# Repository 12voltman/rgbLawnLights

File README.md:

# rgbLawnLights
Circuit boards for a distributed network of individually adressable RGB led bulbs.

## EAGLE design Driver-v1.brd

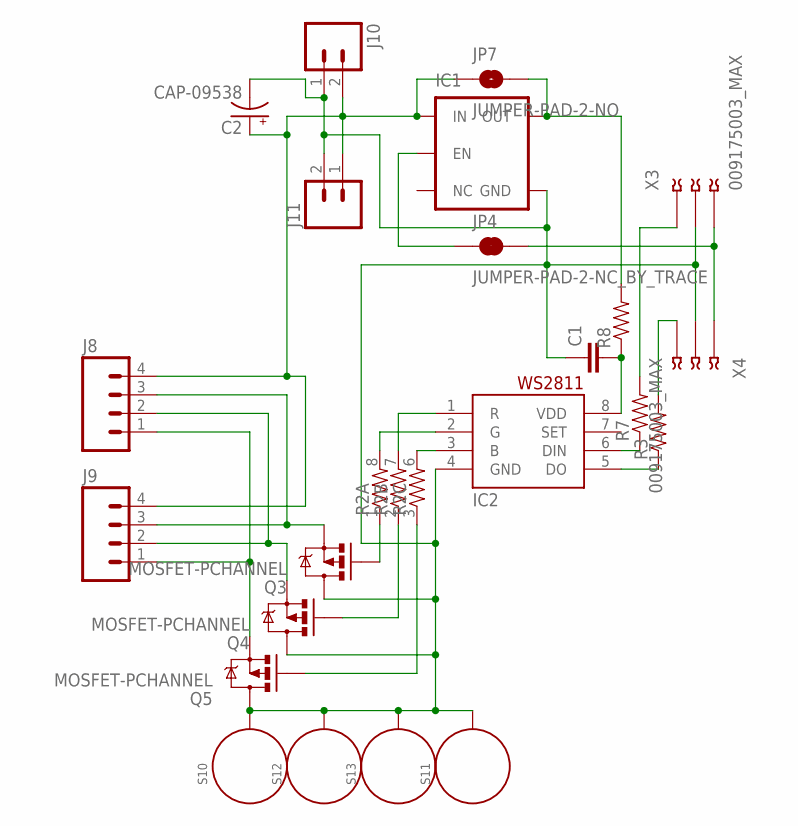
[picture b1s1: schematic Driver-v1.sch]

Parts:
C1: CAP1206; 1206
C2: CAP-09538; CPOL-RADIAL-1000UF-25V
IC1: V_REG_TPS76433SOT23-5; SOT23-5
IC2: WS2811-SOP8; SO08-SKINNYPADS
J8, J9: M04LONGPADS; 1X04_LONGPADS
J10, J11: M025MM; SCREWTERMINAL-5MM-2
JP4: JUMPER-PAD-2-NC_BY_TRACE; PAD-JUMPER-2-NC_BY_TRACE_YES_SILK
JP7: JUMPER-PAD-2-NO; PAD-JUMPER-2-NO_NO_SILK
Q3, Q4, Q5: MOSFET-PCHANNEL; SOT23-3
R2: RESISTOR-ARRAY0603-ARV; 0603-ARV
R3, R7: RESISTOR0603; 0603-RES
R8: RESISTOR0805-RES; 0805
S10, S11, S12, S13: STANDOFF_ELECTRICAL; STANDOFF-ELECTRICAL
X3, X4: 009175003_MAX

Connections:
GND2: C1.1, C2.-, IC1.2 (GND), IC2.4 (GND), J10.1, J11.2, Q3.3 (D), Q4.3 (D), Q5.3 (D), S10.P1, S11.P1, S12.P1, S13.P1, X3.2, X3.2@1 (2), X4.2, X4.2@1 (2)
unnamed: J8.1, J9.1, Q5.2 (S)
unnamed: J8.2, J9.2, Q4.2 (S)
unnamed: J8.3, J9.3, Q3.2 (S)
unnamed: Q3.1 (G), R2.1
unnamed: Q4.1 (G), R2.2 (1)
unnamed: Q5.1 (G), R2.3 (1)
unnamed: JP4.2, X3.3, X3.3@2 (3), X4.1, X4.1@1 (1)
unnamed: IC1.3 (EN), JP4.1
unnamed: R7.2, X3.1, X3.1@1 (1)
unnamed: IC2.5 (DO), R3.1
unnamed: IC2.3 (B), R2.6 (2)
unnamed: IC2.2 (G), R2.8 (2)
unnamed: IC2.1 (R), R2.7 (2)
unnamed: IC1.5 (OUT), JP7.2, R8.2
unnamed: IC2.6 (DIN), R7.1
unnamed: R3.2, X4.3, X4.3@2 (3)
unnamed: C1.2, IC2.8 (VDD), R8.1
VIN2: C2.+, IC1.1 (IN), J8.4, J9.4, J10.2, J11.1, JP7.1

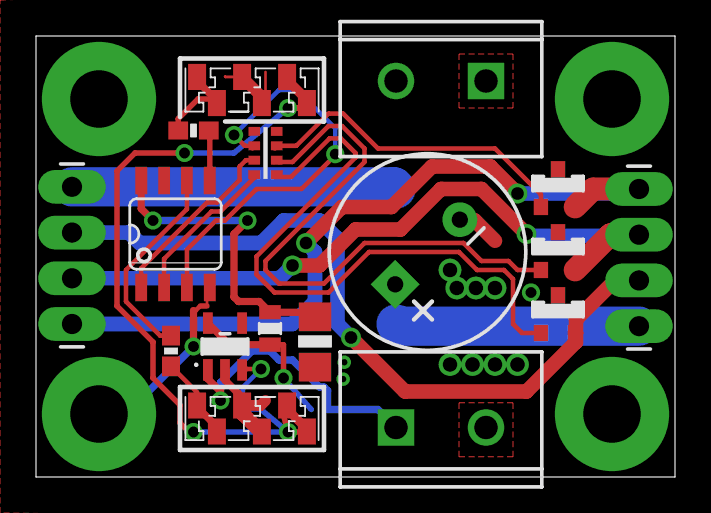
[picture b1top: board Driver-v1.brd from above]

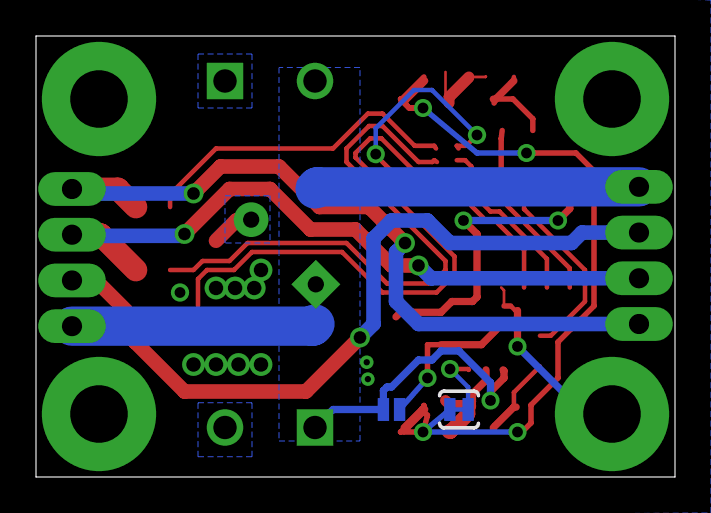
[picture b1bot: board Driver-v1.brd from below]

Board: 2 copper layers, 35.5 x 24.5 mm, 23 parts (2 on the bottom side), 19 nets.

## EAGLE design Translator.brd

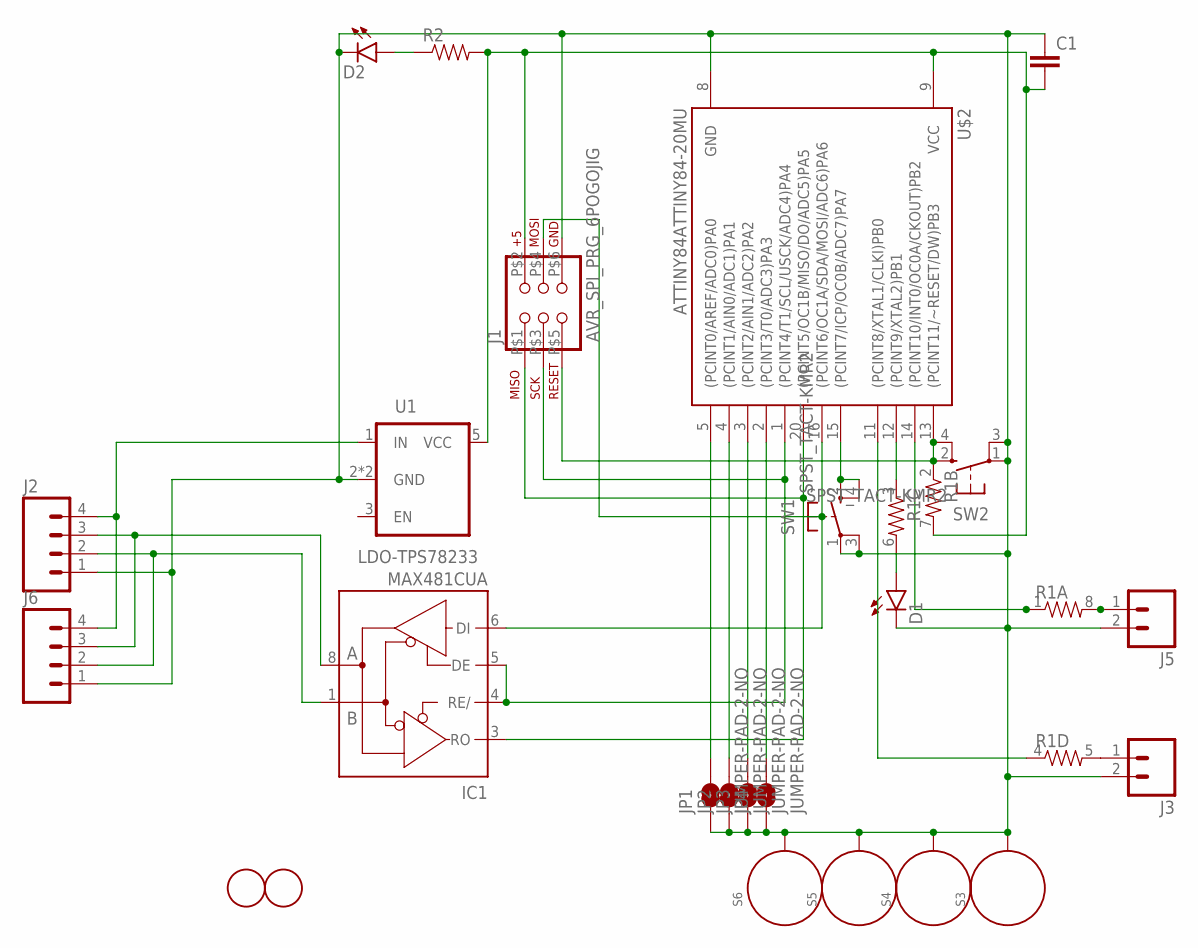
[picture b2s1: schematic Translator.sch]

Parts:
C1: CAP0805; 0805
D1, D2: LED1206; LED-1206
IC1: MAX481CUA; UMAX8
J1: AVR_SPI_PRG_6POGOJIG; 2X3_MAX
J2, J6: M04SCREW; SCREWTERMINAL-3.5MM-4
J3, J5: M025MM; SCREWTERMINAL-5MM-2
JP1, JP2, JP3, JP4: JUMPER-PAD-2-NO; PAD-JUMPER-2-NO_NO_SILK
R1: RESISTOR-ARRAY0603-ARV; 0603-ARV
R2: RESISTOR0805-RES; 0805
S3, S4, S5, S6: STANDOFF_ELECTRICAL; STANDOFF-ELECTRICAL
SW1, SW2: SPST_TACT-KMR2; KMR2
U1: LDO-TPS78233; SOT23-5
U$2: ATTINY84ATTINY84-20MU; QFN20
U$3, U$4: FIDUCIAL; FIDUCIAL_1MM

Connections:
485A: IC1.8 (A), J2.3, J6.3
485B: IC1.1 (B), J2.2, J6.2
FLOW: IC1.4 (RE/), IC1.5 (DE), J1.P$3 (SCK), U$2.1 ((PCINT4/T1/SCL/USCK/ADC4)PA4)
GND: C1.1, D1.C, D2.C, IC1.7 (GND), J1.P$6 (GND), J2.1, J3.2, J5.2, J6.1, JP1.1, JP2.1, JP3.1, JP4.1, S3.P1, S4.P1, S5.P1, S6.P1, SW1.1, SW1.3 (P1), SW2.1, SW2.3 (P1), U1.2 (GND), U1.4 (GND), U$2.8 (GND)
unnamed: JP1.2, U$2.5 ((PCINT0/AREF/ADC0)PA0)
unnamed: R1.3 (1), U$2.12 ((PCINT9/XTAL2)PB1)
unnamed: J3.1, R1.5 (2)
unnamed: JP2.2, U$2.4 ((PCINT1/AIN0/ADC1)PA1)
unnamed: J5.1, R1.8 (2)
unnamed: JP3.2, U$2.3 ((PCINT2/AIN1/ADC2)PA2)
unnamed: JP4.2, U$2.2 ((PCINT3/T0/ADC3)PA3)
unnamed: D1.A, R1.6 (2)
unnamed: SW1.2 (S), SW1.4 (S1), U$2.15 ((PCINT7/ICP/OC0B/ADC7)PA7)
unnamed: D2.A, R2.1
OUT1: R1.1, U$2.14 ((PCINT10/INT0/OC0A/CKOUT)PB2)
OUT3: R1.4 (1), U$2.11 ((PCINT8/XTAL1/CLKI)PB0)
RST: J1.P$5 (RESET), R1.2 (1), SW2.2 (S), SW2.4 (S1), U$2.13 ((PCINT11/~RESET/DW)PB3)
RX: IC1.3 (RO), J1.P$1 (MISO), U$2.20 ((PCINT5/OC1B/MISO/DO/ADC5)PA5)
TX: IC1.6 (DI), J1.P$4 (MOSI), U$2.16 ((PCINT6/OC1A/SDA/MOSI/ADC6)PA6)
VCC: C1.2, IC1.2 (VCC), J1.P$2 (VIN), R1.7 (2), R2.2, U1.5 (VCC), U$2.9 (VCC)
VIN: J2.4, J6.4, U1.1 (IN)

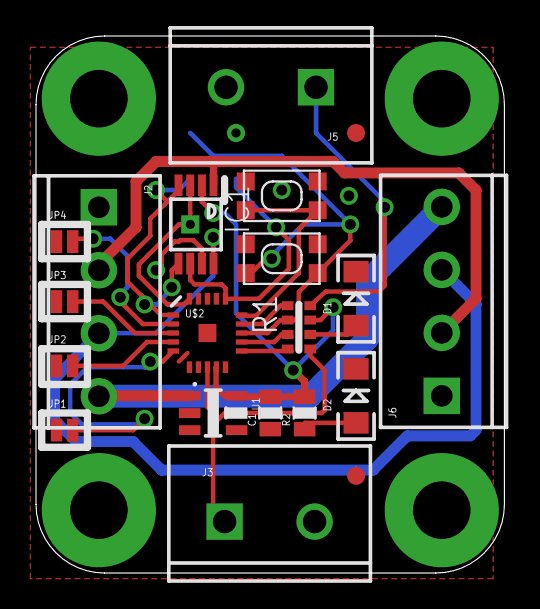
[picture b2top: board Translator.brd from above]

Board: 2 copper layers, 26.0 x 29.8 mm, 25 parts (1 on the bottom side), 21 nets.

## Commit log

2017-11-24 Initial coimmit

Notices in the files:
parts and their libraries:
SparkFun-PowerIC: Licensing: Creative Commons ShareAlike 4.0 International - https://creativecommons.org/licenses/by-sa/4.0
